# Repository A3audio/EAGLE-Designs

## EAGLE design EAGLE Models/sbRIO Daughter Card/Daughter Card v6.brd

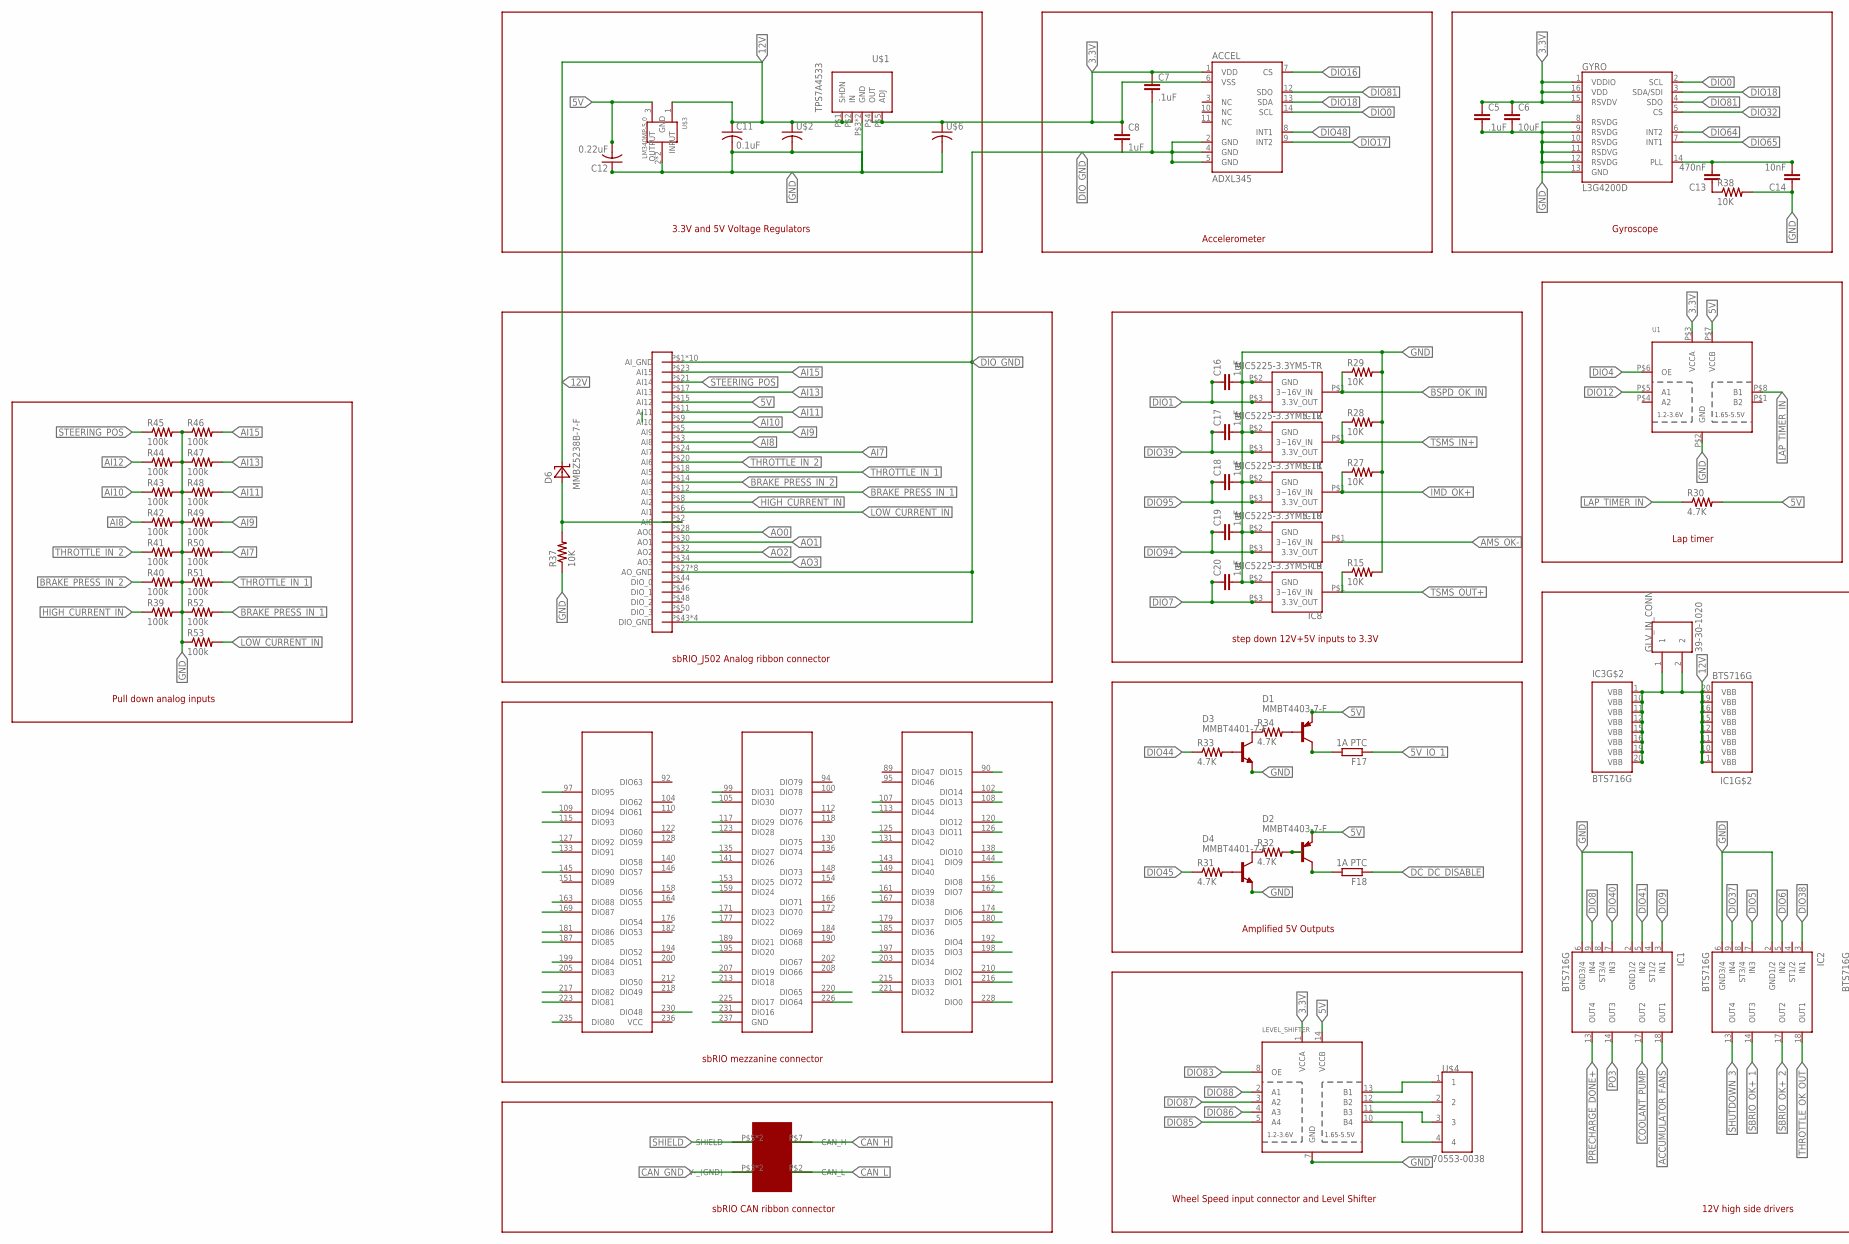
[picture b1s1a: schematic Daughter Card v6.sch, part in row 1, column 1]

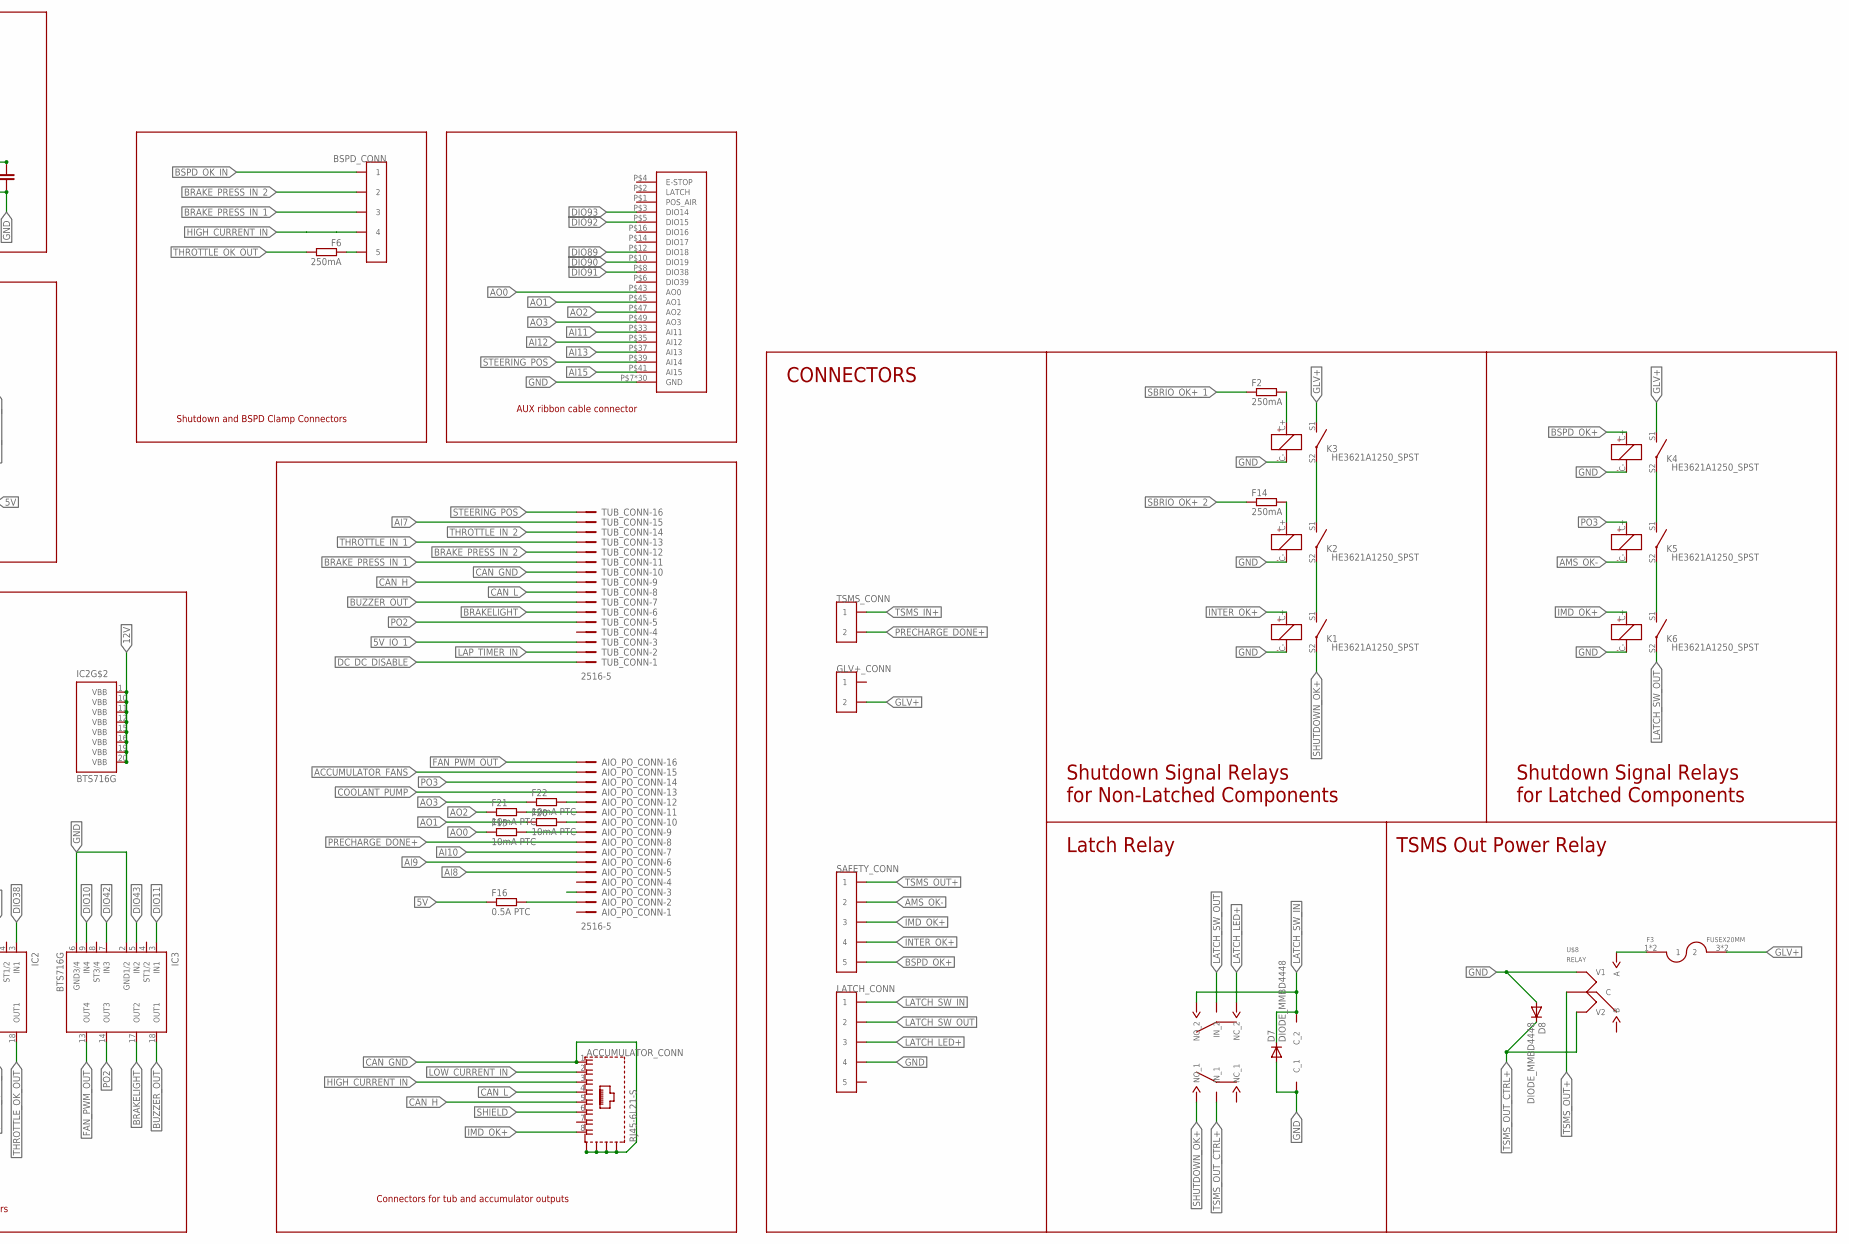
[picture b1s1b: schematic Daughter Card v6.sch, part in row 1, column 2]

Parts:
ACCEL: ADXL345; LGA14
ACCUMULATOR_CONN: RJ45-6L21-S; RJ45-SHIELD1
AIO_PO_CONN: 2516-5; PAK100/2500-5-16
BSPD_CONN: CONN_5; CONNECTOR_5
C5, C7: .1uF; 0603-CAP
C6: 10uF; 0603-CAP
C8, C16, C17, C18, C19, C20: 1uF; 0603-CAP
C11: 0.1uF; C1206
C12: 0.22uF; C1206
C13: 470nF; 0603-CAP
C14: 10nF; 0603-CAP
D1, D2: MMBT4403-7-F; SOT-23-3
D3, D4: MMBT4401-7-F; SOT-23-3
D6: MMBZ5238B-7-F; SOT-23-3
D7, D8: DIODE_MMBD4448; SOT-23-3
F2, F6, F14: 250mA; R0603
F3: FUSEX20MM; FUSE_5MM
F15, F20, F21, F22: 10mA PTC; R0402
F16: 0.5A PTC; R0603
F17, F18: 1A PTC; R0603
GLV+_CONN: CONN_2; CONNECTOR_2
GLV_IN_CONN: 39-30-1020; MOLEX_39-30-1020
GYRO: L3G4200D; LGA16-4X4
IC1, IC2, IC3: BTS716G; PG-DSO-20
IC8, IC9, IC10, IC11, IC12: MIC5225-3.3YM5-TR; SOT-23-3
K1, K2, K3, K4, K5, K6: HE3621A1250_SPST
LATCH_CONN: CONN_5; CONNECTOR_5
LATCH_U7: JW2SN-DC12V; DPDT_JW2_FORM_C
LEVEL_SHIFTER: TXB0104PWR; TSSOP14
R15, R27, R28, R29, R37, R38: 10K; R0603
R30, R31, R32, R33, R34: 4.7K; R0603
R39, R40, R41, R42, R43, R44, R45, R46, R47, R48, R49, R50, R51, R52, R53: 100k; R0603
SAFETY_CONN: CONN_5; CONNECTOR_5
SBRIO_ANALOG: SBRIO_MIO; SBRIO_J502_J503
SBRIO_AUX: SBRIO_AUX; SBRIO_J502_J503
SBRIO_CAN: SBRIO_W500; SBRIO_W
SBRIO_MEZZANINE: SBRIO_RMC; SEAM-40-XX.X-XX-06-X-A
TSMS_CONN: CONN_2; CONNECTOR_2
TUB_CONN: 2516-5; PAK100/2500-5-16
U1: TXS0102; VFSOP-8
U$1: TPS7A4533; DIGIKEY_P-N 490-12344-1-ND
U$2, U$6: C-USC1206; C1206
U$3: LM340MP-5.0; SOT-223-4
U$4: 70553-0038; MOLEX_70553-0038
U$8: RELAY

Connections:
3.3V: ACCEL.1 (VDD), ACCEL.6 (VSS), C5.1, C6.1, C7.1, C8.1, GYRO.1 (VDDIO), GYRO.15 (RSVDV), GYRO.16 (VDD), LEVEL_SHIFTER.1 (VCCA), U1.P$3 (VCCA), U$1.P$4 (OUT), U$1.P$5 (ADJ), U$6.1
5V: C12.2, D1.P$3 (E), D2.P$3 (E), F16.1, LEVEL_SHIFTER.14 (VCCB), R30.2, SBRIO_ANALOG.P$15 (AI12), U1.P$7 (VCCB), U$3.3 (OUTPUT)
5V_IO_1: F17.1, TUB_CONN.3
12V: C11.1, D6.P$1 (C), GLV_IN_CONN.1, GLV_IN_CONN.2, IC1.1 (VBB), IC1.10 (VBB), IC1.11 (VBB), IC1.12 (VBB), IC1.15 (VBB), IC1.16 (VBB), IC1.19 (VBB), IC1.20 (VBB), IC2.1 (VBB), IC2.10 (VBB), IC2.11 (VBB), IC2.12 (VBB), IC2.15 (VBB), IC2.16 (VBB), IC2.19 (VBB), IC2.20 (VBB), IC3.1 (VBB), IC3.10 (VBB), IC3.11 (VBB), IC3.12 (VBB), IC3.15 (VBB), IC3.16 (VBB), IC3.19 (VBB), IC3.20 (VBB), U$1.P$1 (SHDN), U$1.P$2 (IN), U$2.1, U$3.1 (INPUT)
ACCUMULATOR_FANS: AIO_PO_CONN.15, IC1.18 (OUT1)
AI7: R50.2, SBRIO_ANALOG.P$24 (AI7), TUB_CONN.15
AI8: AIO_PO_CONN.5, R42.1, SBRIO_ANALOG.P$3 (AI8)
AI9: AIO_PO_CONN.6, R49.2, SBRIO_ANALOG.P$5 (AI9)
AI10: AIO_PO_CONN.7, R43.1, SBRIO_ANALOG.P$9 (AI10)
AI11: R48.2, SBRIO_ANALOG.P$11 (AI11), SBRIO_AUX.P$33 (AI11)
AI12: R44.1, SBRIO_AUX.P$35 (AI12)
AI13: R47.2, SBRIO_ANALOG.P$17 (AI13), SBRIO_AUX.P$37 (AI13)
AI15: R46.2, SBRIO_ANALOG.P$23 (AI15), SBRIO_AUX.P$41 (AI15)
AMS_OK-: IC9.P$1 (3~16V_IN), K5.C-, SAFETY_CONN.3 (2), SAFETY_CONN.4 (2)
AO0: F15.1, SBRIO_ANALOG.P$28 (AO0), SBRIO_AUX.P$43 (AO0)
AO1: F20.1, SBRIO_ANALOG.P$30 (AO1), SBRIO_AUX.P$45 (AO1)
AO2: F21.1, SBRIO_ANALOG.P$32 (AO2), SBRIO_AUX.P$47 (AO2)
AO3: F22.1, SBRIO_ANALOG.P$34 (AO3), SBRIO_AUX.P$49 (AO3)
BRAKELIGHT: IC3.17 (OUT2), TUB_CONN.6
BRAKE_PRESS_IN_1: BSPD_CONN.5 (3), BSPD_CONN.6 (3), R52.2, SBRIO_ANALOG.P$12 (AI3), TUB_CONN.11
BRAKE_PRESS_IN_2: BSPD_CONN.3 (2), BSPD_CONN.4 (2), R40.1, SBRIO_ANALOG.P$14 (AI4), TUB_CONN.12
BSPD_OK+: K4.C+, SAFETY_CONN.9 (5), SAFETY_CONN.10 (5)
BSPD_OK_IN: BSPD_CONN.1, BSPD_CONN.2 (1), IC12.P$1 (3~16V_IN), R29.1
BUZZER_OUT: IC3.18 (OUT1), TUB_CONN.7
CAN_GND: ACCUMULATOR_CONN.1, ACCUMULATOR_CONN.S1 (S), ACCUMULATOR_CONN.S2 (S), ACCUMULATOR_CONN.S3 (S), ACCUMULATOR_CONN.S4 (S), SBRIO_CAN.P$3 (V-_(GND)), SBRIO_CAN.P$6 (V-_(GND)), TUB_CONN.10
CAN_H: ACCUMULATOR_CONN.5, SBRIO_CAN.P$7 (CAN_H), TUB_CONN.9
CAN_L: ACCUMULATOR_CONN.4, SBRIO_CAN.P$2 (CAN_L), TUB_CONN.8
COOLANT_PUMP: AIO_PO_CONN.13, IC1.17 (OUT2)
DC_DC_DISABLE: F18.1, TUB_CONN.1
DIO0: ACCEL.14 (SCL), GYRO.2 (SCL), SBRIO_MEZZANINE.228 (DIO0)
DIO1: C16.1, IC12.P$3 (3.3V_OUT), SBRIO_MEZZANINE.216 (DIO1)
DIO2: SBRIO_MEZZANINE.210 (DIO2)
DIO3: SBRIO_MEZZANINE.198 (DIO3)
DIO4: SBRIO_MEZZANINE.192 (DIO4), U1.P$6 (OE)
DIO5: IC2.7 (IN3), SBRIO_MEZZANINE.180 (DIO5)
DIO6: IC2.5 (IN2), SBRIO_MEZZANINE.174 (DIO6)
DIO7: C20.1, IC8.P$3 (3.3V_OUT), SBRIO_MEZZANINE.162 (DIO7)
DIO8: IC1.9 (IN4), SBRIO_MEZZANINE.156 (DIO8)
DIO9: IC1.3 (IN1), SBRIO_MEZZANINE.144 (DIO9)
DIO10: IC3.9 (IN4), SBRIO_MEZZANINE.138 (DIO10)
DIO11: IC3.3 (IN1), SBRIO_MEZZANINE.126 (DIO11)
DIO12: SBRIO_MEZZANINE.120 (DIO12), U1.P$5 (A1)
DIO13: SBRIO_MEZZANINE.108 (DIO13)
DIO14: SBRIO_MEZZANINE.102 (DIO14)
DIO15: SBRIO_MEZZANINE.90 (DIO15)
DIO16: ACCEL.7 (CS), SBRIO_MEZZANINE.231 (DIO16)
DIO17: ACCEL.9 (INT2), SBRIO_MEZZANINE.225 (DIO17)
DIO18: ACCEL.13 (SDA), GYRO.3 (SDA/SDI), SBRIO_MEZZANINE.213 (DIO18)
DIO19: SBRIO_MEZZANINE.207 (DIO19)
DIO20: SBRIO_MEZZANINE.195 (DIO20)
DIO21: SBRIO_MEZZANINE.189 (DIO21)
DIO22: SBRIO_MEZZANINE.177 (DIO22)
DIO23: SBRIO_MEZZANINE.171 (DIO23)
DIO24: SBRIO_MEZZANINE.159 (DIO24)
DIO25: SBRIO_MEZZANINE.153 (DIO25)
DIO26: SBRIO_MEZZANINE.141 (DIO26)
DIO27: SBRIO_MEZZANINE.135 (DIO27)
DIO28: SBRIO_MEZZANINE.123 (DIO28)
DIO29: SBRIO_MEZZANINE.117 (DIO29)
DIO30: SBRIO_MEZZANINE.105 (DIO30)
DIO31: SBRIO_MEZZANINE.99 (DIO31)
DIO32: GYRO.5 (CS), SBRIO_MEZZANINE.221 (DIO32)
DIO33: SBRIO_MEZZANINE.215 (DIO33)
DIO34: SBRIO_MEZZANINE.203 (DIO34)
DIO35: SBRIO_MEZZANINE.197 (DIO35)
DIO36: SBRIO_MEZZANINE.185 (DIO36)
DIO37: IC2.9 (IN4), SBRIO_MEZZANINE.179 (DIO37)
DIO38: IC2.3 (IN1), SBRIO_MEZZANINE.167 (DIO38)
DIO39: C17.1, IC11.P$3 (3.3V_OUT), SBRIO_MEZZANINE.161 (DIO39)
DIO40: IC1.7 (IN3), SBRIO_MEZZANINE.149 (DIO40)
DIO41: IC1.5 (IN2), SBRIO_MEZZANINE.143 (DIO41)
DIO42: IC3.7 (IN3), SBRIO_MEZZANINE.131 (DIO42)
DIO43: IC3.5 (IN2), SBRIO_MEZZANINE.125 (DIO43)
DIO44: R33.1, SBRIO_MEZZANINE.113 (DIO44)
DIO45: R31.1, SBRIO_MEZZANINE.107 (DIO45)
DIO48: ACCEL.8 (INT1), SBRIO_MEZZANINE.230 (DIO48)
DIO64: GYRO.6 (INT2), SBRIO_MEZZANINE.226 (DIO64)
DIO65: GYRO.7 (INT1), SBRIO_MEZZANINE.220 (DIO65)
DIO80: SBRIO_MEZZANINE.235 (DIO80)
DIO81: ACCEL.12 (SDO), GYRO.4 (SDO), SBRIO_MEZZANINE.223 (DIO81)
DIO82: SBRIO_MEZZANINE.217 (DIO82)
DIO83: LEVEL_SHIFTER.8 (OE), SBRIO_MEZZANINE.205 (DIO83)
DIO84: SBRIO_MEZZANINE.199 (DIO84)
DIO85: LEVEL_SHIFTER.5 (A4), SBRIO_MEZZANINE.187 (DIO85)
DIO86: LEVEL_SHIFTER.4 (A3), SBRIO_MEZZANINE.181 (DIO86)
DIO87: LEVEL_SHIFTER.3 (A2), SBRIO_MEZZANINE.169 (DIO87)
DIO88: LEVEL_SHIFTER.2 (A1), SBRIO_MEZZANINE.163 (DIO88)
DIO89: SBRIO_AUX.P$12 (DIO18)
DIO90: SBRIO_AUX.P$10 (DIO19), SBRIO_MEZZANINE.145 (DIO90)
DIO91: SBRIO_AUX.P$8 (DIO38), SBRIO_MEZZANINE.133 (DIO91)
DIO92: SBRIO_AUX.P$5 (DIO15), SBRIO_MEZZANINE.127 (DIO92)
DIO93: SBRIO_AUX.P$3 (DIO14), SBRIO_MEZZANINE.115 (DIO93)
DIO94: C19.1, IC9.P$3 (3.3V_OUT), SBRIO_MEZZANINE.109 (DIO94)
DIO95: C18.1, IC10.P$3 (3.3V_OUT), SBRIO_MEZZANINE.97 (DIO95)
DIO_GND: ACCEL.2 (GND), ACCEL.4 (GND), ACCEL.5 (GND), C7.2, C8.2, SBRIO_ANALOG.P$1 (AI_GND), SBRIO_ANALOG.P$4 (AI_GND), SBRIO_ANALOG.P$7 (AI_GND), SBRIO_ANALOG.P$10 (AI_GND), SBRIO_ANALOG.P$13 (AI_GND), SBRIO_ANALOG.P$16 (AI_GND), SBRIO_ANALOG.P$19 (AI_GND), SBRIO_ANALOG.P$22 (AI_GND), SBRIO_ANALOG.P$25 (AI_GND), SBRIO_ANALOG.P$26 (AI_GND), SBRIO_ANALOG.P$27 (AO_GND), SBRIO_ANALOG.P$29 (AO_GND), SBRIO_ANALOG.P$31 (AO_GND), SBRIO_ANALOG.P$33 (AO_GND), SBRIO_ANALOG.P$35 (AO_GND), SBRIO_ANALOG.P$37 (AO_GND), SBRIO_ANALOG.P$39 (AO_GND), SBRIO_ANALOG.P$41 (AO_GND), SBRIO_ANALOG.P$43 (DIO_GND), SBRIO_ANALOG.P$45 (DIO_GND), SBRIO_ANALOG.P$47 (DIO_GND), SBRIO_ANALOG.P$49 (DIO_GND)
FAN_PWM_OUT: AIO_PO_CONN.16, IC3.13 (OUT4)
GLV+: F3.3 (2), F3.4 (2), GLV+_CONN.3 (2), GLV+_CONN.4 (2), K3.S1 (SW_1), K4.S1 (SW_1)
GND: C5.2, C6.2, C11.2, C12.1, C14.1, C16.2, C17.2, C18.2, C19.2, C20.2, D3.P$3 (E), D4.P$3 (E), D7.P$2 (A), D8.P$2 (A), GYRO.8 (RSVDG), GYRO.9 (RSVDG), GYRO.10 (RSVDG), GYRO.11 (RSDVG), GYRO.12 (RSVDG), GYRO.13 (GND), IC1.2 (GND1/2), IC1.6 (GND3/4), IC2.2 (GND1/2), IC2.6 (GND3/4), IC3.2 (GND1/2), IC3.6 (GND3/4), IC8.P$2 (GND), IC9.P$2 (GND), IC10.P$2 (GND), IC11.P$2 (GND), IC12.P$2 (GND), K1.C-, K2.C-, K3.C-, K4.C-, K6.C-, LATCH_CONN.7 (4), LATCH_CONN.8 (4), LATCH_U7.COIL_1 (C_1), LEVEL_SHIFTER.7 (GND), R15.2, R27.2, R28.2, R29.2, R37.1, R38.2, R39.2, R40.2, R41.2, R42.2, R43.2, R44.2, R45.2, R46.1, R47.1, R48.1, R49.1, R50.1, R51.1, R52.1, R53.1, SBRIO_AUX.P$7 (GND), SBRIO_AUX.P$9 (GND), SBRIO_AUX.P$11 (GND), SBRIO_AUX.P$13 (GND), SBRIO_AUX.P$15 (GND), SBRIO_AUX.P$17 (GND), SBRIO_AUX.P$18 (GND), SBRIO_AUX.P$19 (GND), SBRIO_AUX.P$20 (GND), SBRIO_AUX.P$21 (GND), SBRIO_AUX.P$22 (GND), SBRIO_AUX.P$23 (GND), SBRIO_AUX.P$24 (GND), SBRIO_AUX.P$25 (GND), SBRIO_AUX.P$26 (GND), SBRIO_AUX.P$27 (GND), SBRIO_AUX.P$28 (GND), SBRIO_AUX.P$29 (GND), SBRIO_AUX.P$30 (GND), SBRIO_AUX.P$31 (GND), SBRIO_AUX.P$32 (GND), SBRIO_AUX.P$34 (GND), SBRIO_AUX.P$36 (GND), SBRIO_AUX.P$38 (GND), SBRIO_AUX.P$40 (GND), SBRIO_AUX.P$42 (GND), SBRIO_AUX.P$44 (GND), SBRIO_AUX.P$46 (GND), SBRIO_AUX.P$48 (GND), SBRIO_AUX.P$50 (GND), SBRIO_MEZZANINE.237 (GND), U1.P$2 (GND), U$1.P$3 (GND), U$1.P$6 (GND), U$2.2, U$3.2 (GND), U$3.4 (GND), U$6.2, U$8.V1
HIGH_CURRENT_IN: ACCUMULATOR_CONN.3, BSPD_CONN.7 (4), BSPD_CONN.8 (4), R39.1, SBRIO_ANALOG.P$8 (AI2)
IMD_OK+: ACCUMULATOR_CONN.8, IC10.P$1 (3~16V_IN), K6.C+, R27.1, SAFETY_CONN.5 (3), SAFETY_CONN.6 (3)
INTER_OK+: K1.C+, SAFETY_CONN.7 (4), SAFETY_CONN.8 (4)
K4: K4.S2 (SW_2), K5.S1 (SW_1)
LAP_TIMER_IN: R30.1, TUB_CONN.2, U1.P$8 (B1)
LATCH_LED+: LATCH_CONN.5 (3), LATCH_CONN.6 (3), LATCH_U7.NC_2
LATCH_SW_IN: D7.P$1 (C), LATCH_CONN.1, LATCH_CONN.2 (1), LATCH_U7.COIL_2 (C_2), LATCH_U7.NO_2
LATCH_SW_OUT: K6.S2 (SW_2), LATCH_CONN.3 (2), LATCH_CONN.4 (2), LATCH_U7.CENTER_2 (IN_2)
LOW_CURRENT_IN: ACCUMULATOR_CONN.2, R53.2, SBRIO_ANALOG.P$6 (AI1)
unnamed: K2.S1 (SW_1), K3.S2 (SW_2)
unnamed: AIO_PO_CONN.9, F15.2
unnamed: D6.P$2 (A), R37.2, SBRIO_ANALOG.P$2 (AI0)
unnamed: AIO_PO_CONN.10, F20.2
unnamed: K1.S1 (SW_1), K2.S2 (SW_2)
unnamed: AIO_PO_CONN.11, F21.2
unnamed: AIO_PO_CONN.12, F22.2
unnamed: K5.S2 (SW_2), K6.S1 (SW_1)
unnamed: F3.1, F3.2 (1), U$8.A
unnamed: D4.P$1 (C), R32.1
unnamed: D4.P$2 (B), R31.2
unnamed: AIO_PO_CONN.2, F16.2
unnamed: D3.P$2 (B), R33.2
unnamed: D1.P$2 (B), R34.2
unnamed: D3.P$1 (C), R34.1
unnamed: C13.1, R38.1
unnamed: C13.2, C14.2, GYRO.14 (PLL)
unnamed: D1.P$1 (C), F17.2
unnamed: D2.P$1 (C), F18.2
unnamed: D2.P$2 (B), R32.2
PO2: IC3.14 (OUT3), TUB_CONN.5
PO3: AIO_PO_CONN.14, IC1.14 (OUT3), K5.C+
PRECHARGE_DONE+: AIO_PO_CONN.8, IC1.13 (OUT4), TSMS_CONN.3 (2), TSMS_CONN.4 (2)
SBRIO_OK+_1: F2.1, IC2.14 (OUT3)
SBRIO_OK+_1_RELAY_IN: F2.2, K3.C+
SBRIO_OK+_2: F14.1, IC2.17 (OUT2)
SBRIO_OK_2_RELAY: F14.2, K2.C+
SHIELD: ACCUMULATOR_CONN.6, SBRIO_CAN.P$5 (SHIELD), SBRIO_CAN.P$10 (SHIELD)
SHUTDOWN_3: IC2.13 (OUT4)
SHUTDOWN_OK+: K1.S2 (SW_2), LATCH_U7.NO_1
STEERING_POS: R45.1, SBRIO_ANALOG.P$21 (AI14), SBRIO_AUX.P$39 (AI14), TUB_CONN.16
THROTTLE_IN_1: R51.2, SBRIO_ANALOG.P$18 (AI5), TUB_CONN.13
THROTTLE_IN_2: R41.1, SBRIO_ANALOG.P$20 (AI6), TUB_CONN.14
THROTTLE_OK_OUT: F6.2, IC2.18 (OUT1)
THROTTLE_OK_OUT_FUSED: BSPD_CONN.9 (5), BSPD_CONN.10 (5), F6.1
TSMS_IN+: IC11.P$1 (3~16V_IN), R28.1, TSMS_CONN.1, TSMS_CONN.2 (1)
TSMS_OUT+: IC8.P$1 (3~16V_IN), R15.1, SAFETY_CONN.1, SAFETY_CONN.2 (1), U$8.CENTER (C)
TSMS_OUT_CTRL+: D8.P$1 (C), LATCH_U7.CENTER_1 (IN_1), U$8.V2
VCC: SBRIO_MEZZANINE.236 (VCC)
WS1: LEVEL_SHIFTER.13 (B1), U$4.1
WS2: LEVEL_SHIFTER.12 (B2), U$4.2
WS3: LEVEL_SHIFTER.11 (B3), U$4.3
WS4: LEVEL_SHIFTER.10 (B4), U$4.4

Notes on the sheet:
step down 12V+5V inputs to 3.3V
AUX ribbon cable connector
Amplified 5V Outputs
sbRIO CAN ribbon connector
sbRIO mezzanine connector
sbRIO_J502 Analog ribbon connector
Gyroscope
3.3V and 5V Voltage Regulators
Accelerometer
Wheel Speed input connector and Level Shifter
Shutdown and BSPD Clamp Connectors
12V high side drivers
Lap timer
Connectors for tub and accumulator outputs
Pull down analog inputs
CONNECTORS
Shutdown Signal Relays for Non-Latched Components
Shutdown Signal Relays for Latched Components
Latch Relay
TSMS Out Power Relay

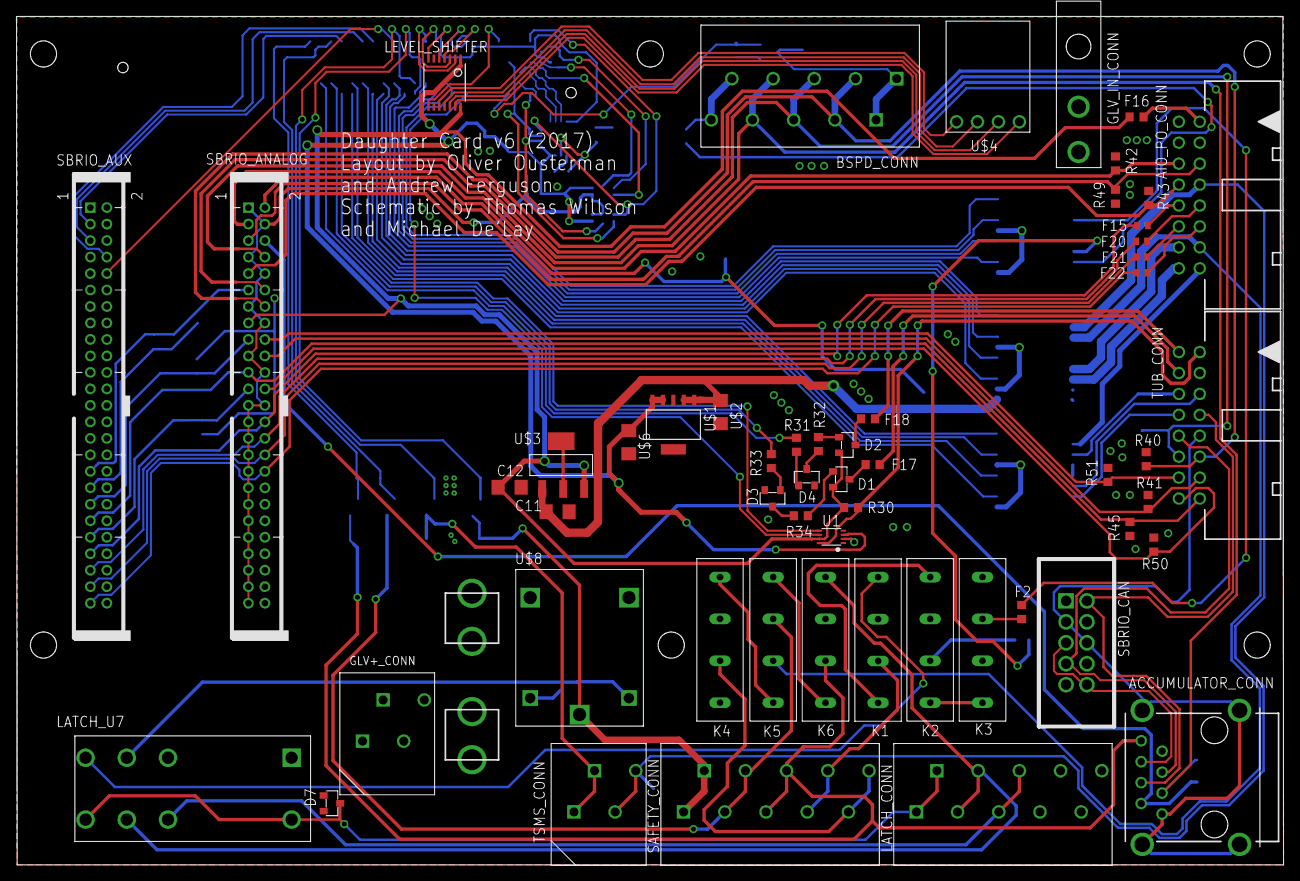
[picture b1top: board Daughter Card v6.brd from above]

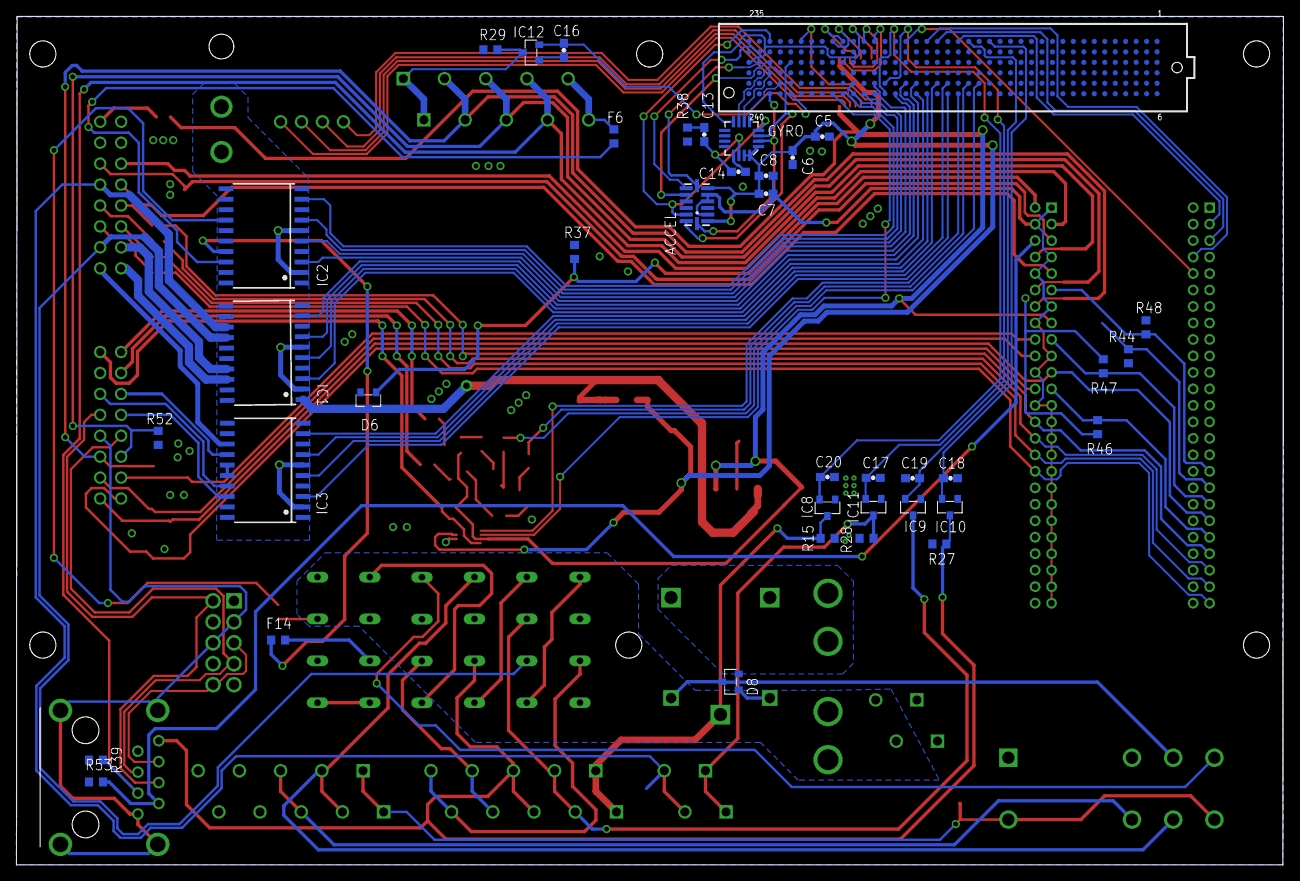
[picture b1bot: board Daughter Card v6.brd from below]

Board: 2 copper layers, 153.7 x 102.9 mm, 95 parts (39 on the bottom side), 122 nets.

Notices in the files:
parts and their libraries:
SparkFun-Aesthetics: Licensing: CC v3.0 Share-Alike You are welcome to use this library for commercial purposes.
